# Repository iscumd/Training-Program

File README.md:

# Training-Program
A place for organizing training program related stuff

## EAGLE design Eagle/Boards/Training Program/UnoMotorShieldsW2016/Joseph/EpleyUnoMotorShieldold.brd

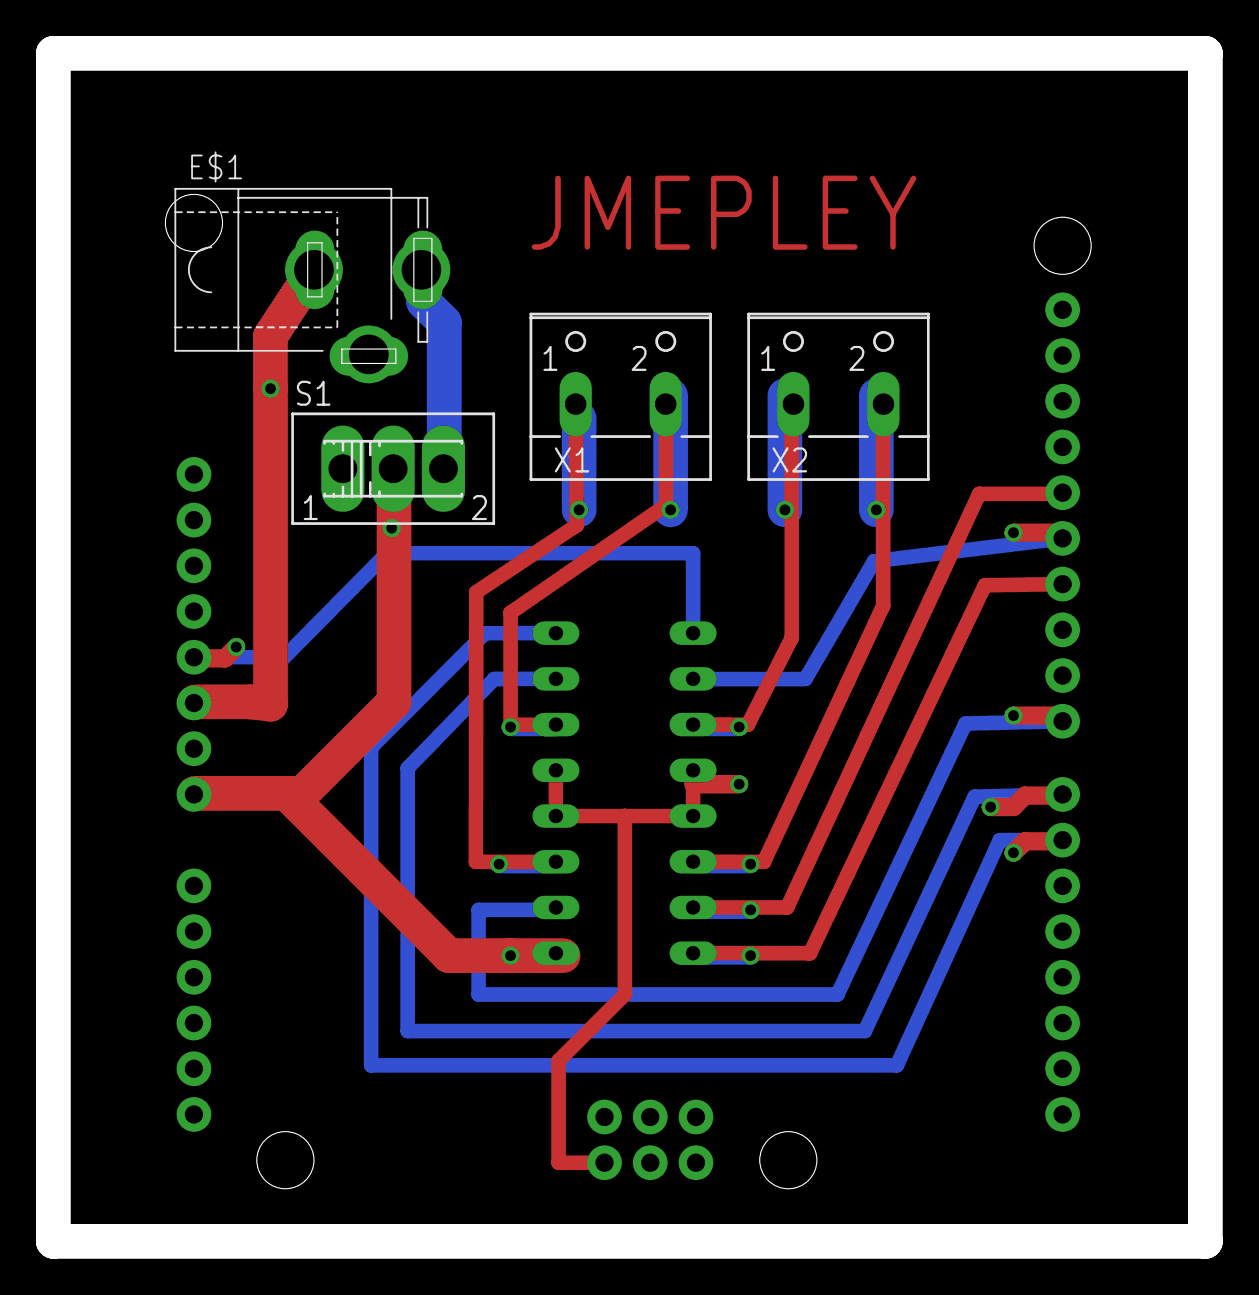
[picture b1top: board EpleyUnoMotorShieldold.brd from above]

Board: 2 copper layers, 64.0 x 66.0 mm, 6 parts (0 on the bottom side), 13 nets.

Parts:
E$1: 5.5-2.5-BARRELCONNECTOR
J1: ARDUINO_UNO_R3; ARDUINO_R3
S1: SLIDE_SWITCH
U$1: MOTOR_DRIVERDIP16; DIP16
X1, X2: 2PIN-SCREW-TERMINAL

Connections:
1A: J1.D7, U$1.P2
2A: J1.D8, U$1.P7
3A: J1.D13, U$1.P10
4A: J1.D12, U$1.P15
EN1: J1.D6, U$1.P1
EN2: J1.D11, U$1.P9
GND: J1.GND@4, U$1.P4, U$1.P5, U$1.P12, U$1.P13
unnamed: U$1.P6, X1.1
unnamed: U$1.P3, X1.2
unnamed: U$1.P14, X2.1
unnamed: U$1.P11, X2.2
unnamed: J1.5V, U$1.P16
unnamed: J1.VIN, U$1.P8

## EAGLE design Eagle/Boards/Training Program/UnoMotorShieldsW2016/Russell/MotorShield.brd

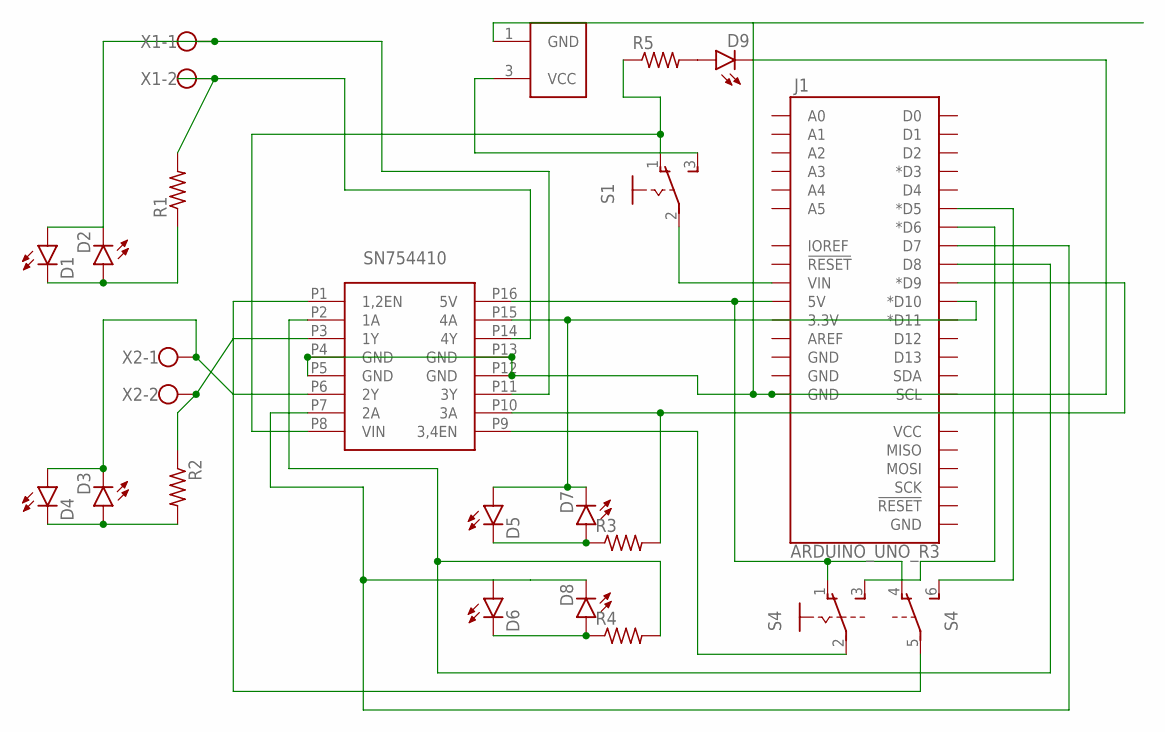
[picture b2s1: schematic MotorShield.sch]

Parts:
D1, D2, D3, D4, D5, D6, D7, D8, D9: LED3MM
J1: ARDUINO_UNO_R3; ARDUINO_R3
R1, R2, R3, R4, R5: RESISTOR0204/7; 0204/7
S1: SLIDE_SWITCH
S4: DUAL_SLIDE_SWITCH
U$1: MOTOR_DRIVERDIP16; DIP16
U$2: BARREL_CONNECTOR; 5.5-2.5-BARRELCONNECTOR
X1, X2: SCREWCONNECTOR; 2PIN-SCREW-TERMINAL

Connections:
unnamed: R2.1, U$1.P3 (1Y), X2.2
unnamed: R1.2, U$1.P14 (4Y), X1.2
unnamed: J1.VIN, S1.2
unnamed: D6.A, D8.K (C), J1.D7, U$1.P7 (2A)
unnamed: R5.1, S1.1 (O), U$1.P8 (VIN)
unnamed: D5.A, D7.K (C), J1.D10 (*D10), U$1.P15 (4A)
unnamed: S4.2, U$1.P9 (3,4EN)
unnamed: D3.K (C), D4.A, U$1.P6 (2Y), X2.1
unnamed: J1.D8, R4.2, U$1.P2 (1A)
unnamed: J1.D9 (*D9), R3.2, U$1.P10 (3A)
unnamed: D9.A, R5.2
unnamed: J1.D5 (*D5), S4.6 (S)
unnamed: S4.5, U$1.P1 (1,2EN)
unnamed: J1.D6 (*D6), S4.3 (S)
unnamed: D3.A, D4.K (C), R2.2
unnamed: D5.K (C), D7.A, R3.1
unnamed: D1.A, D2.K (C), U$1.P11 (3Y), X1.1
unnamed: D1.K (C), D2.A, R1.1
unnamed: J1.5V, S4.1 (O), S4.4 (O), U$1.P16 (5V)
unnamed: D9.K (C), J1.GND@2 (GND), U$1.P4 (GND), U$1.P5 (GND), U$1.P12 (GND), U$1.P13 (GND), U$2.1 (GND)
unnamed: D6.K (C), D8.A, R4.1
unnamed: S1.3 (S), U$2.3 (VCC)

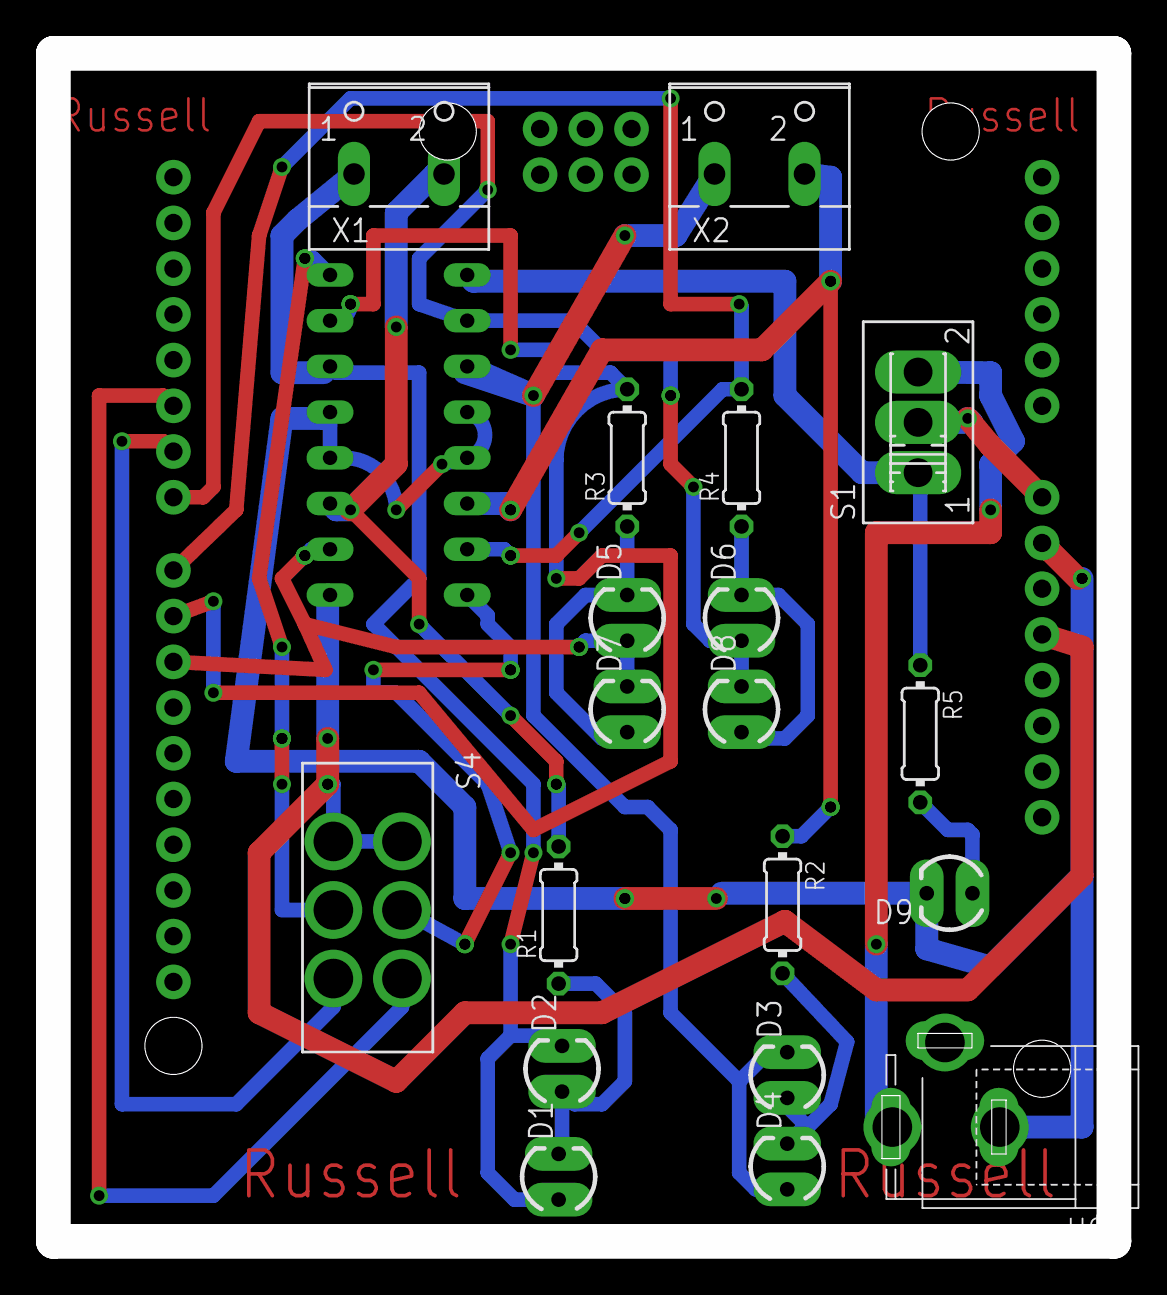
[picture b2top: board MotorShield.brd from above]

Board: 2 copper layers, 58.9 x 66.0 mm, 21 parts (0 on the bottom side), 22 nets.

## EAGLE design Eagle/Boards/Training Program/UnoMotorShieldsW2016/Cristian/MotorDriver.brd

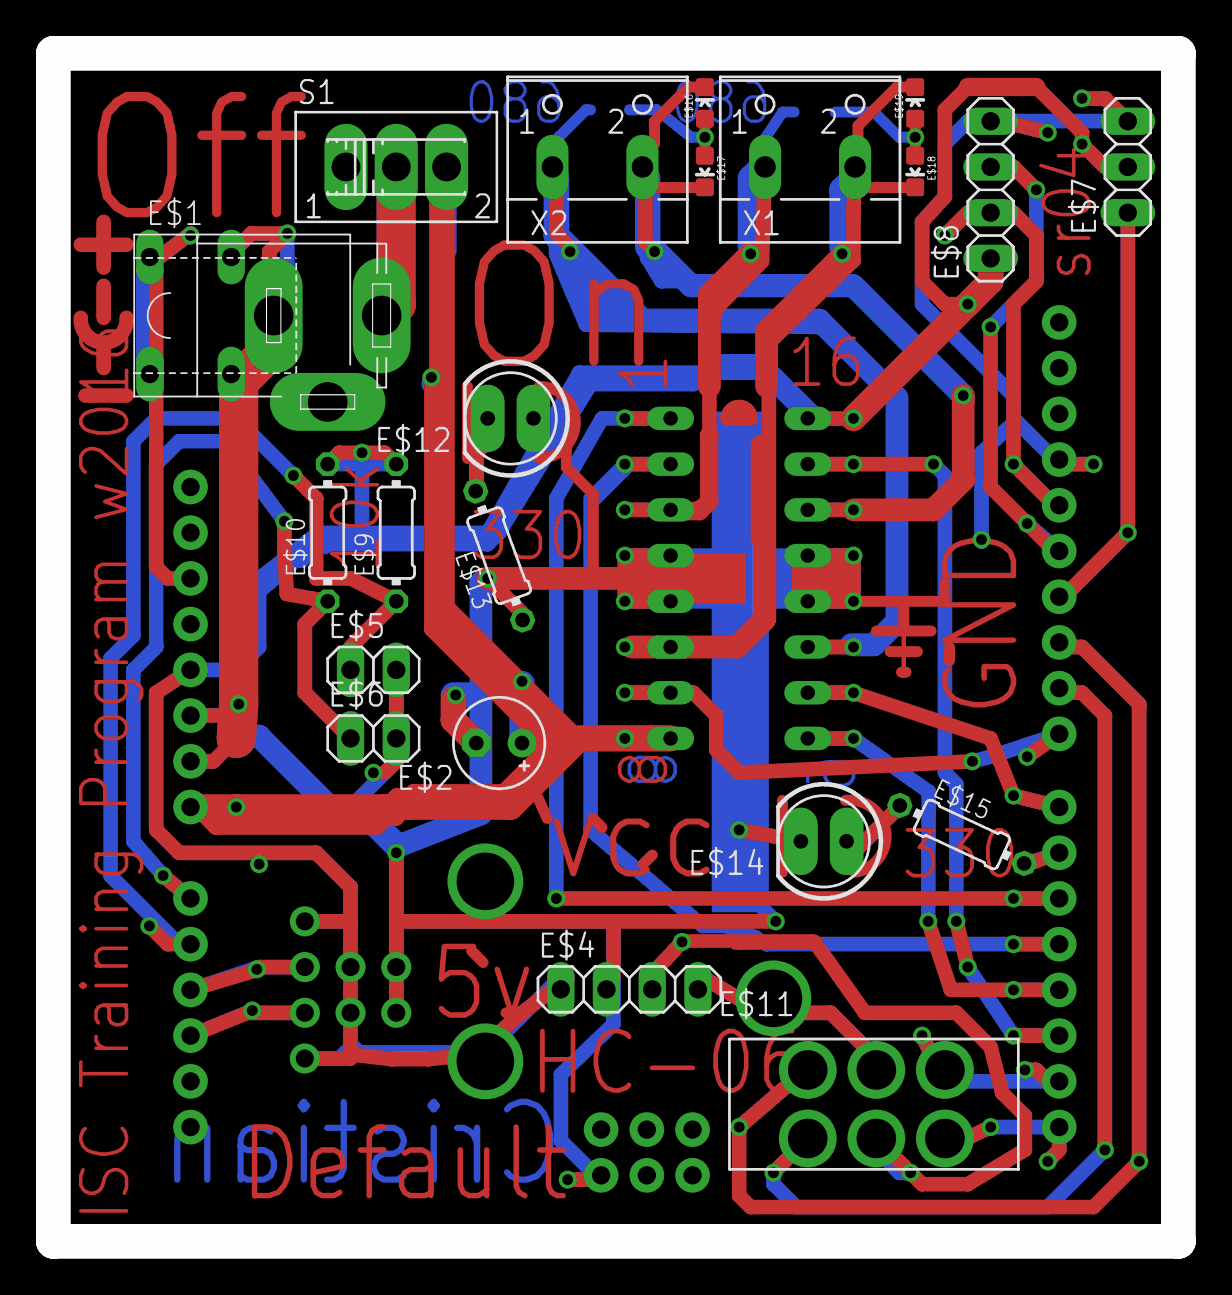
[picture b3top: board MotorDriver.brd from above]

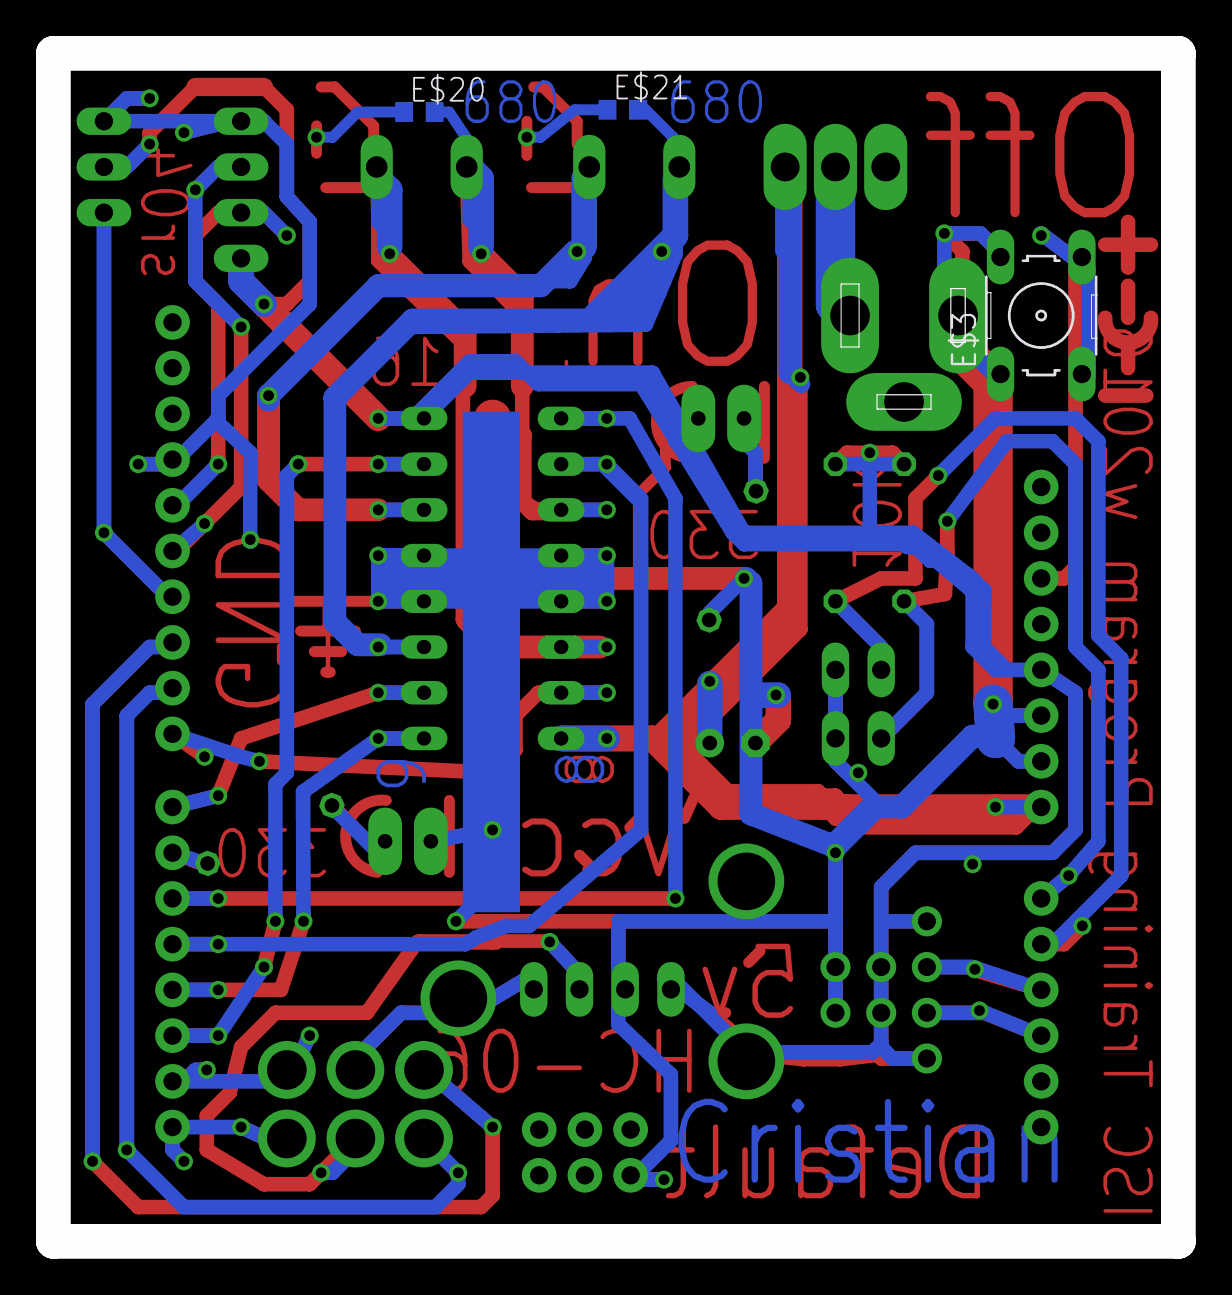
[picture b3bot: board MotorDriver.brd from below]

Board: 2 copper layers, 62.5 x 66.0 mm, 26 parts (3 on the bottom side), 17 nets.

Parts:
E$1: 5.5-2.5-BARRELCONNECTOR
E$2: E2,5-5
E$3: BUTTON
E$4, E$8: 1X04
E$5, E$6: 1X02
E$7: 1X03
E$9, E$10, E$13, E$15: 0204/7
E$11: DUAL_SLIDE_SWITCH
E$12, E$14: LED5MM
E$16, E$17, E$18, E$19: LED-0603
E$20, E$21: R0603
J1: ARDUINO_UNO_R3; ARDUINO_R3
S1: SLIDE_SWITCH
U$1: MOTOR_DRIVERDIP16; DIP16
X1, X2: 2PIN-SCREW-TERMINAL

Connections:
unnamed: U$1.P6, X1.2
unnamed: U$1.P14, X2.2
unnamed: U$1.P11, X2.1
unnamed: E$8.1, E$9.2, E$10.2, J1.5V, U$1.P16
unnamed: E$5.2, J1.GND@2
unnamed: J1.VIN, S1.3, U$1.P8
unnamed: J1.D2, U$1.P15
unnamed: J1.D3, U$1.P9
unnamed: J1.D7, U$1.P10
unnamed: J1.D5, U$1.P1
unnamed: U$1.P3, X1.1
unnamed: J1.D8, U$1.P7
S$4: E$7.3, E$8.4
S$11: E$9.1, J1.A1
S$12: E$6.1, E$10.1, J1.A0
S$49: E$15.2, J1.D6
S$66: U$1.P4, U$1.P5, U$1.P12, U$1.P13

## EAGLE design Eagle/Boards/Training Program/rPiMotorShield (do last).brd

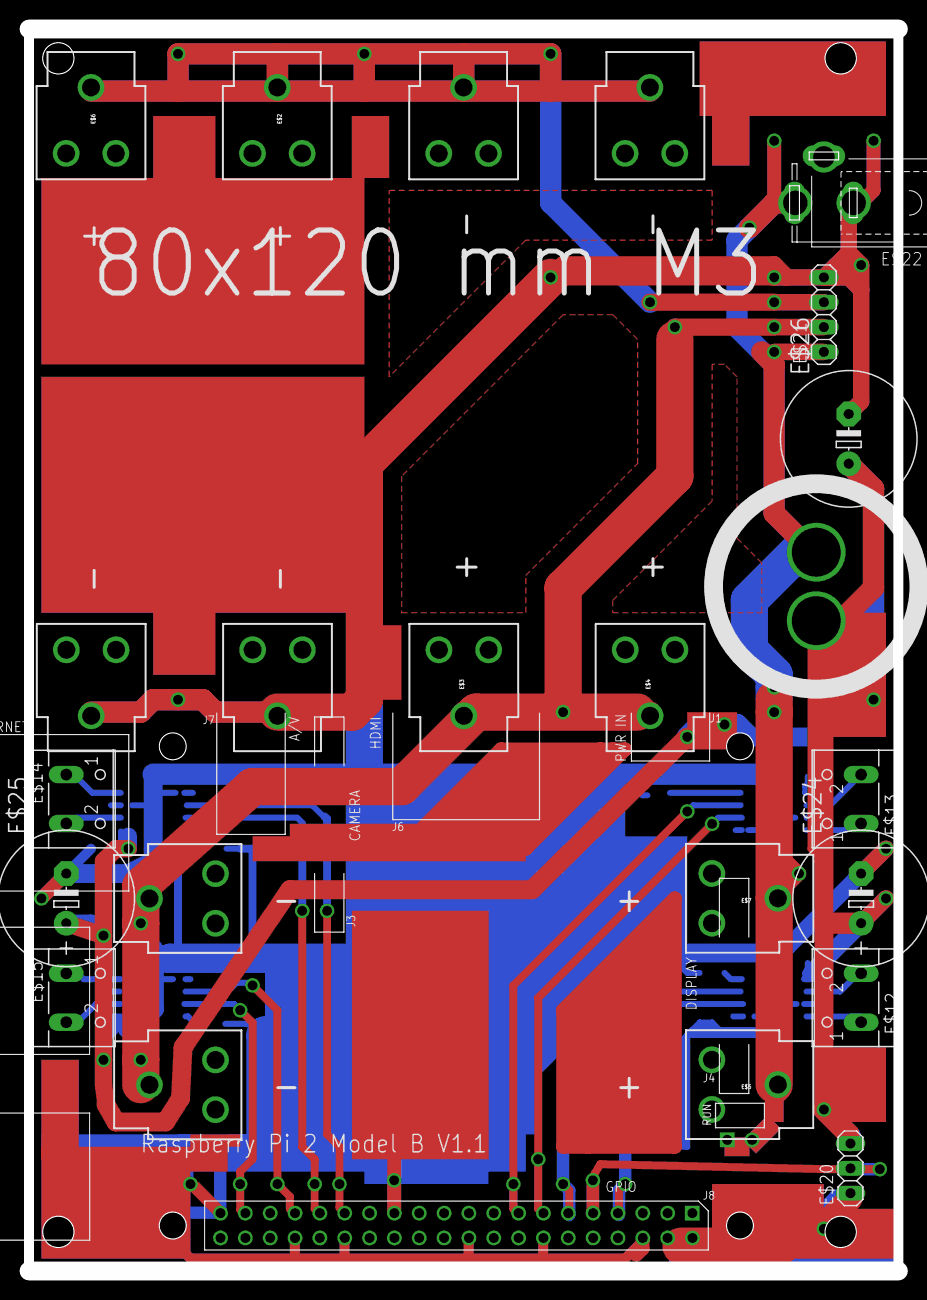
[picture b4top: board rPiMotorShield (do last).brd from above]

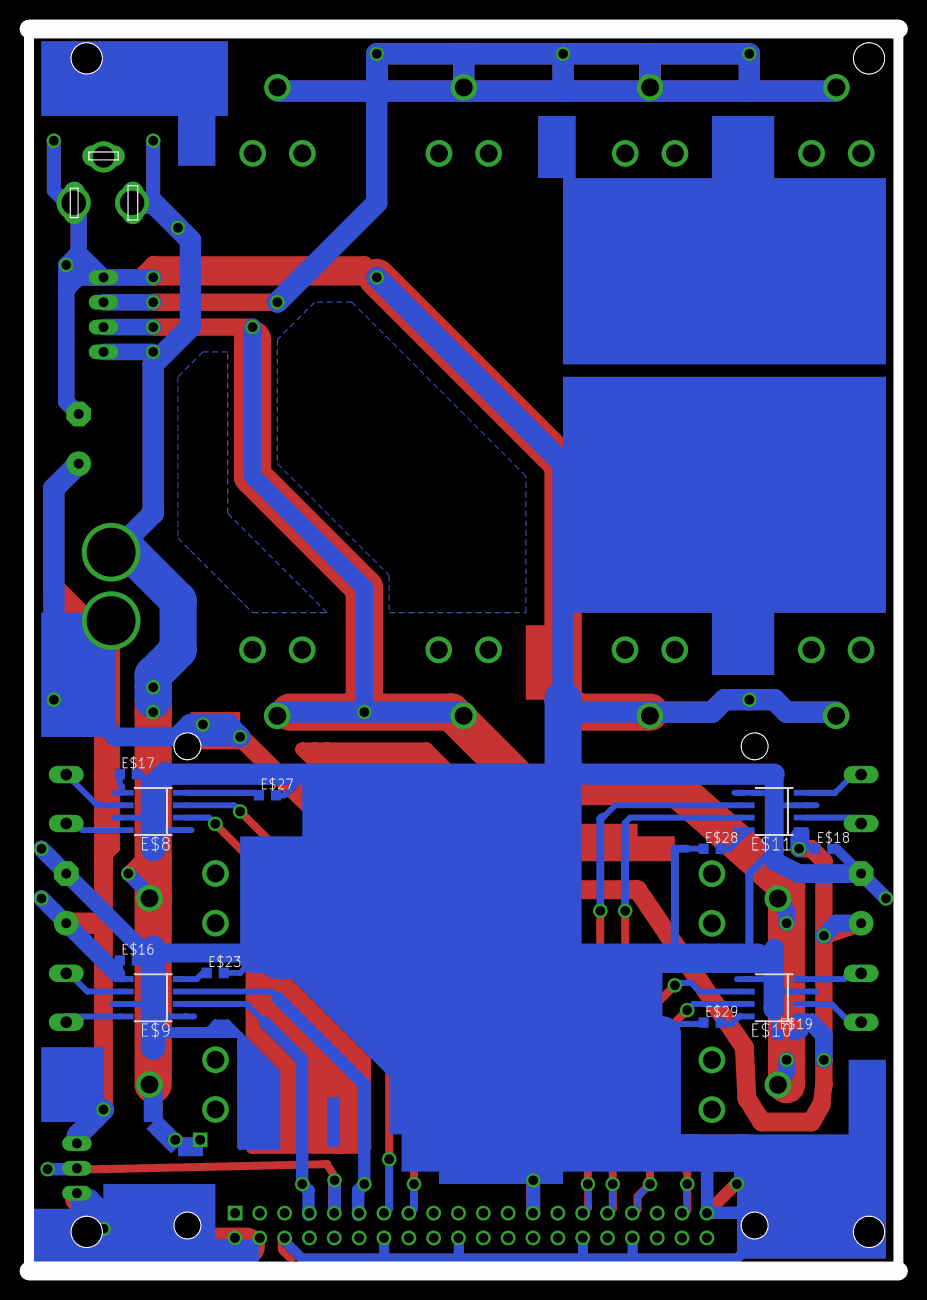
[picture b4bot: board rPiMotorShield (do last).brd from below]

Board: 2 copper layers, 88.9 x 127.0 mm, 29 parts (12 on the bottom side), 2 nets.

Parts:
E$1: RPI2
E$2, E$3, E$4, E$5, E$6, E$7: BATTERY_18650-HOLDER
E$8, E$9, E$10, E$11: D_R-PDSO-G8
E$12, E$13, E$14, E$15: 2PIN-SCREW-TERMINAL
E$16, E$17, E$18, E$19, E$23, E$27, E$28, E$29: C0603K
E$20: 1X03
E$21: 1X04
E$22: 5.5-2.5-BARRELCONNECTOR
E$24, E$25, E$26: E5-13

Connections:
S$24: E$21.4, E$26.-
S$37: E$24.+, E$25.+, E$26.+

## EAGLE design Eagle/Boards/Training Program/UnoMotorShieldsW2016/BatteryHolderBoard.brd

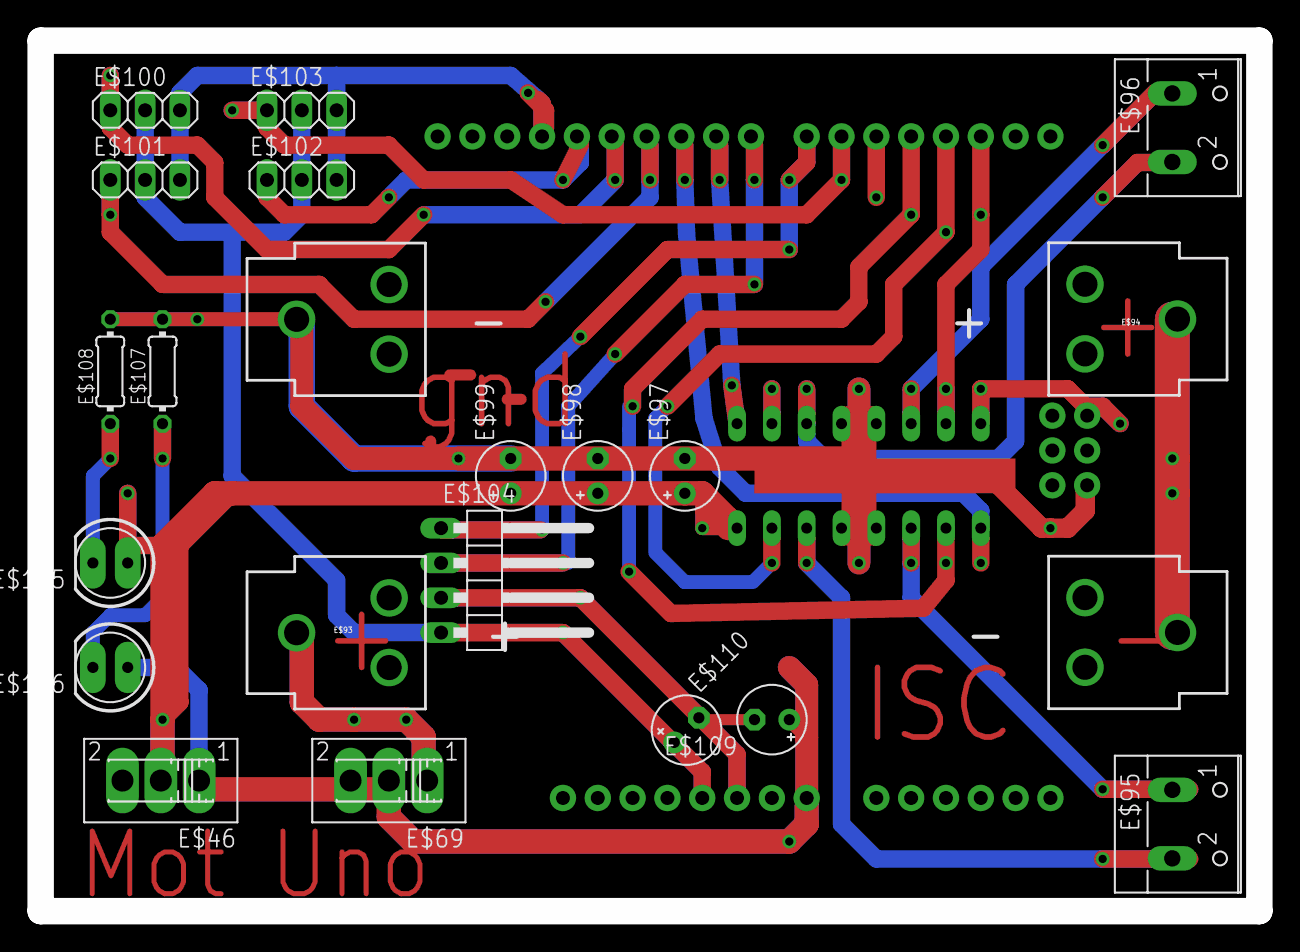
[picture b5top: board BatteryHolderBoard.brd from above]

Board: 2 copper layers, 88.9 x 63.5 mm, 22 parts (1 on the bottom side), 5 nets.

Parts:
E$23: ARDUINO_R3
E$46, E$69: SLIDE_SWITCH
E$92: DIP16
E$93, E$94: BATTERY_18650-HOLDER
E$95, E$96: 2PIN-SCREW-TERMINAL
E$97, E$98, E$99, E$109, E$110: E2,5-5
E$100, E$101, E$102, E$103: 1X03
E$104: 1X04/90
E$105, E$106: LED5MM
E$107, E$108: 0204/7

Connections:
S$60: E$92.P8, E$97.+
S$226: E$100.2, E$103.2, E$104.4
S$227: E$101.3, E$102.3
S$239: E$104.3, E$109.-
S$247: E$106.K, E$107.1

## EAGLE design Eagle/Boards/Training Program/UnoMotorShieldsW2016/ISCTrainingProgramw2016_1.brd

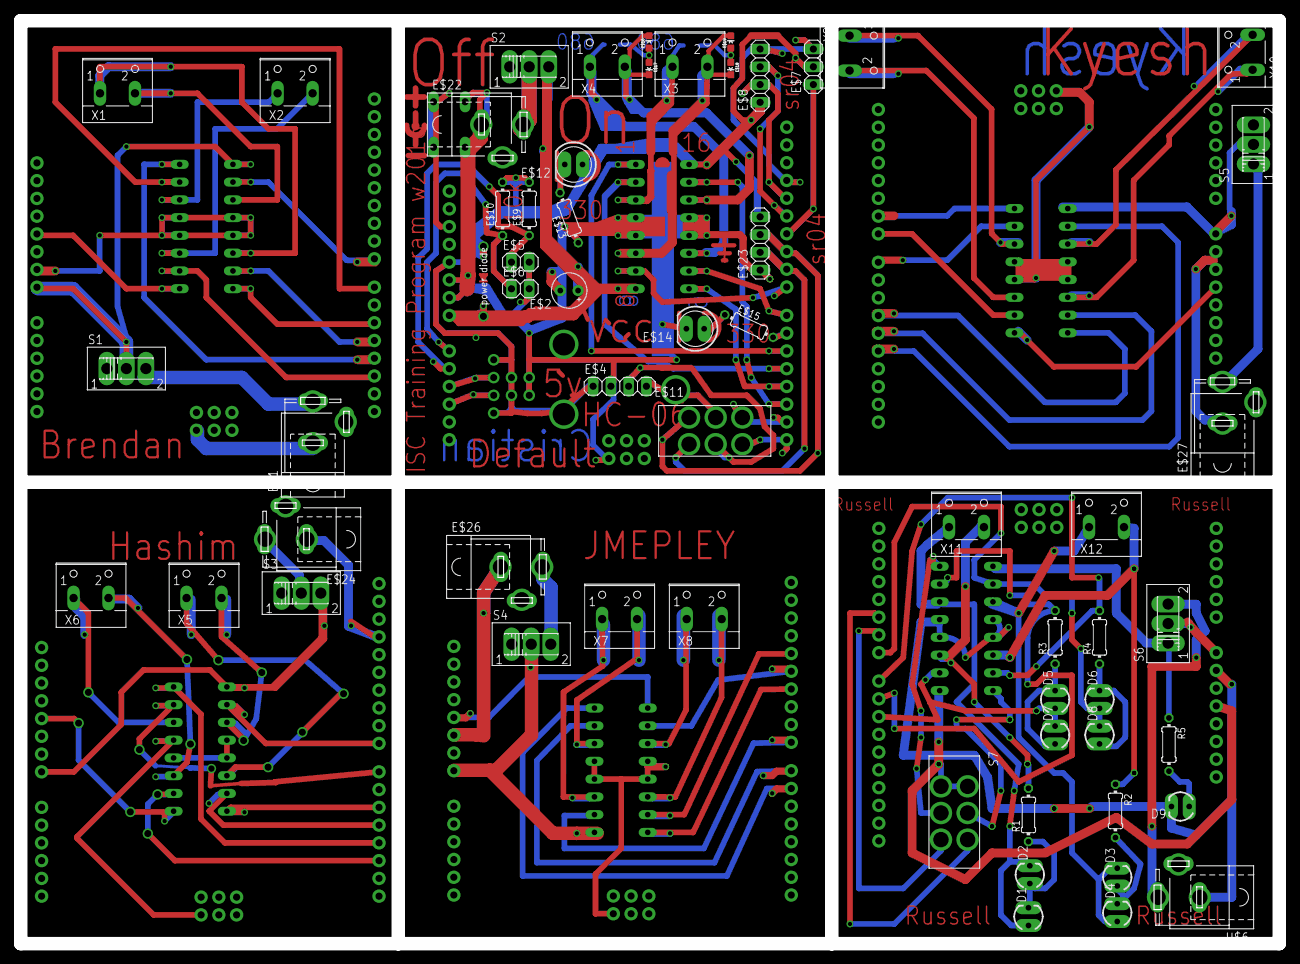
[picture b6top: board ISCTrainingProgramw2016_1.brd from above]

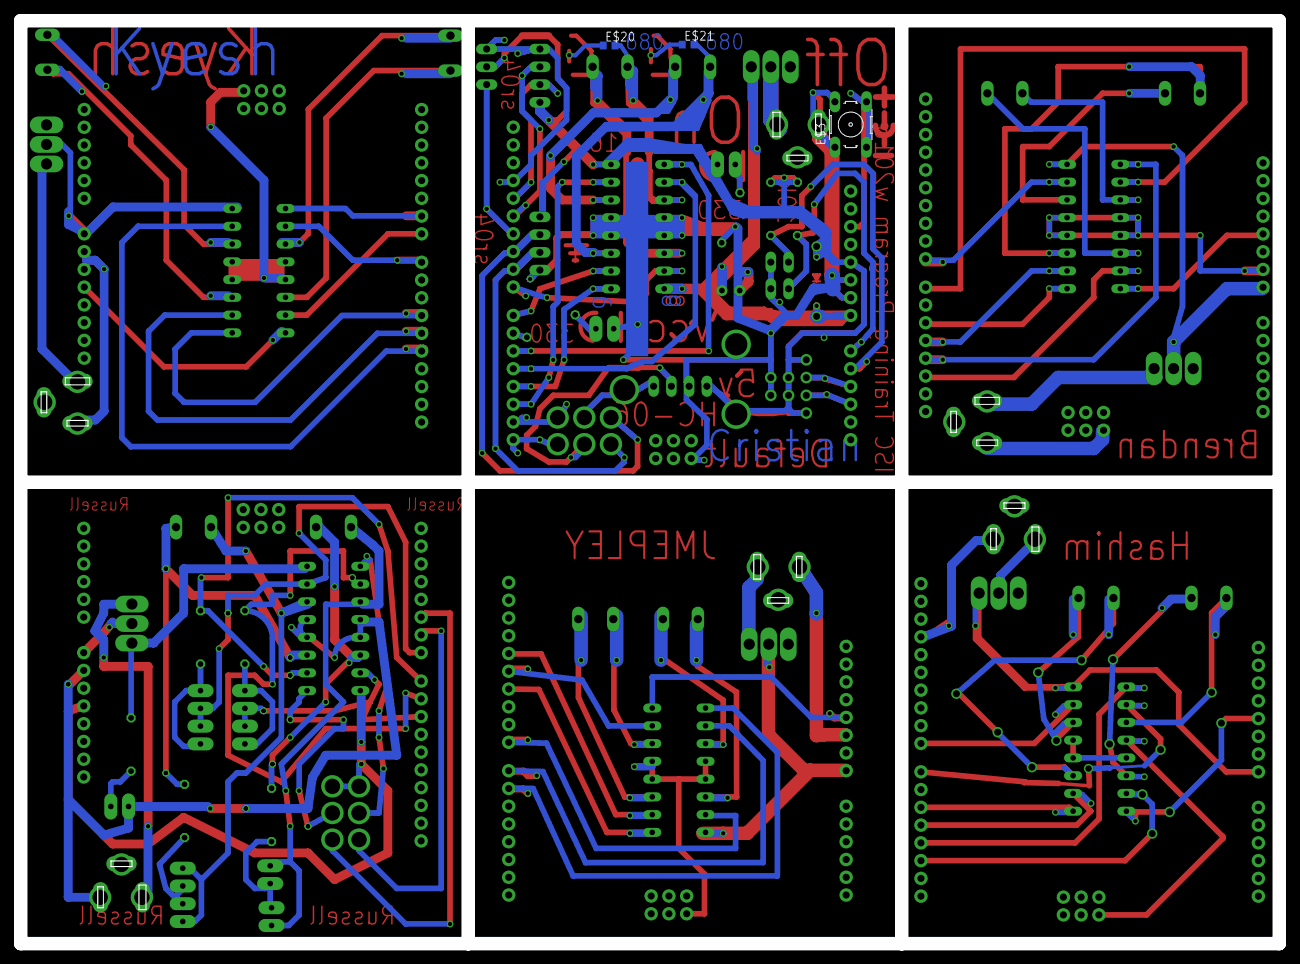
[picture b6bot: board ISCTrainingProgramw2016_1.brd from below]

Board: 2 copper layers, 180.0 x 132.0 mm, 72 parts (3 on the bottom side), 84 nets.

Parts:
D1, D2, D3, D4, D5, D6, D7, D8, D9: LED3MM
E$1, E$22, E$24, E$26, E$27: 5.5-2.5-BARRELCONNECTOR
E$2: E2,5-5
E$3: BUTTON
E$4, E$8, E$23: 1X04
E$5, E$6: 1X02
E$7: 1X03
E$9, E$10, E$13, E$15: 0204/7
E$11: DUAL_SLIDE_SWITCH
E$12, E$14: LED5MM
E$16, E$17, E$18, E$19: LED-0603
E$20, E$21: R0603
E$25: ARDUINO_R3
ENABLE: MOTOR_DRIVERDIP16; DIP16
J1, J2, J3, J4, J5: ARDUINO_UNO_R3; ARDUINO_R3
R1, R2, R3, R4, R5: 0204/7
S1, S2, S3, S4, S5, S6: SLIDE_SWITCH
S7: DUAL_SLIDE_SWITCH
U$1, U$2, U$3, U$4, U$5: MOTOR_DRIVERDIP16; DIP16
U$6: BARREL_CONNECTOR; 5.5-2.5-BARRELCONNECTOR
X1, X2, X3, X4, X5, X6, X7, X8, X9, X10, X11, X12: 2PIN-SCREW-TERMINAL

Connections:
1A: J3.D7, U$4.P2
2A2: J3.D8, U$4.P7
3A2: J3.D13, U$4.P10
4A2: J3.D12, U$4.P15
EN5: J3.D11, U$4.P9
EN6: J3.D6, U$4.P1
ENABLE: ENABLE.P1, J4.D11
GND: U$3.P4, U$3.P5, U$3.P13
GND1: J3.GND@4, U$4.P4, U$4.P5, U$4.P12, U$4.P13
GND4: ENABLE.P4, ENABLE.P5, ENABLE.P12
unnamed: U$1.P3, X1.1
unnamed: U$1.P6, X1.2
unnamed: U$1.P11, X2.1
unnamed: U$1.P14, X2.2
unnamed: U$1.P4, U$1.P5, U$1.P12, U$1.P13
unnamed: U$2.P6, X3.2
unnamed: U$2.P14, X4.2
unnamed: U$2.P11, X4.1
unnamed: E$8.1, E$9.2, E$10.2, J1.5V, U$2.P16
unnamed: E$5.2, J1.GND@2
unnamed: J1.VIN, S2.3, U$2.P8
unnamed: J1.D2, U$2.P15
unnamed: J1.D3, U$2.P9
unnamed: J1.D7, U$2.P10
unnamed: J1.D5, U$2.P1
unnamed: U$2.P3, X3.1
unnamed: J1.D8, U$2.P7
unnamed: U$3.P3, X5.1
unnamed: U$3.P6, X5.2
unnamed: U$3.P11, X6.1
unnamed: U$3.P14, X6.2
unnamed: J2.5V, U$3.P16
unnamed: J2.GND@4, U$3.P12
unnamed: J2.VIN, S3.3, U$3.P8
unnamed: J2.D2, U$3.P15
unnamed: J2.D3, U$3.P9
unnamed: J2.D8, U$3.P7
unnamed: J2.D7, U$3.P10
unnamed: J2.D4, U$3.P2
unnamed: J2.D5, U$3.P1
unnamed: U$4.P6, X7.1
unnamed: U$4.P3, X7.2
unnamed: U$4.P14, X8.1
unnamed: U$4.P11, X8.2
unnamed: J3.5V, U$4.P16
unnamed: J3.VIN, U$4.P8
unnamed: ENABLE.P3, X10.1
unnamed: ENABLE.P13, J4.GND@4
unnamed: ENABLE.P16, J4.5V
unnamed: ENABLE.P8, J4.VIN
unnamed: ENABLE.P6, X10.2
unnamed: ENABLE.P11, X9.1
unnamed: ENABLE.P14, X9.2
unnamed: ENABLE.P2, J4.D12
unnamed: ENABLE.P7, J4.D13
unnamed: ENABLE.P9, J4.D6
unnamed: ENABLE.P15, J4.D7
unnamed: ENABLE.P10, J4.D8
unnamed: R2.1, U$5.P3, X12.2
unnamed: R1.2, X11.2
unnamed: R5.1, S6.1, U$5.P8
unnamed: J5.D8, R4.2, U$5.P2
unnamed: J5.D9, R3.2, U$5.P10
unnamed: S7.5, U$5.P1
unnamed: J5.D5, S7.6
unnamed: J5.D6, S7.3
unnamed: D3.K, D4.A, U$5.P6, X12.1
unnamed: D3.A, D4.K, R2.2
unnamed: D1.A, D2.K, U$5.P11, X11.1
unnamed: D1.K, D2.A, R1.1
unnamed: D5.K, D7.A, R3.1
unnamed: J5.5V, S7.1, S7.4, U$5.P16
unnamed: D5.A, D7.K, J5.D10, U$5.P15
unnamed: D6.K, D8.A, R4.1
unnamed: D6.A, D8.K, J5.D7, U$5.P7
unnamed: D9.A, R5.2
unnamed: D9.K, J5.GND@2, U$5.P12, U$5.P13, U$6.1
unnamed: S6.3, U$6.3
S$28: E$7.3, E$8.4
S$33: E$9.1, J1.A1
S$34: E$6.1, E$10.1, J1.A0
S$66: U$2.P4, U$2.P5, U$2.P12, U$2.P13
S$69: E$15.2, J1.D6
S$197: U$5.P4, U$5.P5

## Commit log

2016-03-26 PCB workshop upload
2016-03-26 added russell's board
2016-03-26 updated sample motor driver shield to add directional LEDs
2016-03-26 updated barrel connector part
2016-03-27 moved barrel connector schematic
2016-03-27 compiled 1st board for fabrication
2016-03-30 enlarged barrel connector footprint
2016-03-30 added default board
2016-03-31 updated Joseph's board
2016-04-28 added rpi boards
2016-07-27 added blinky stuff
2016-07-27 fixed diagram
2016-08-03 added button LED
